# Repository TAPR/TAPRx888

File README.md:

CI docs for design

Source: design @ 3424534723b9f9df8152389dafcadae15212970f
Run: https://github.com/TAPR/TAPRx888/actions/runs/41220624196

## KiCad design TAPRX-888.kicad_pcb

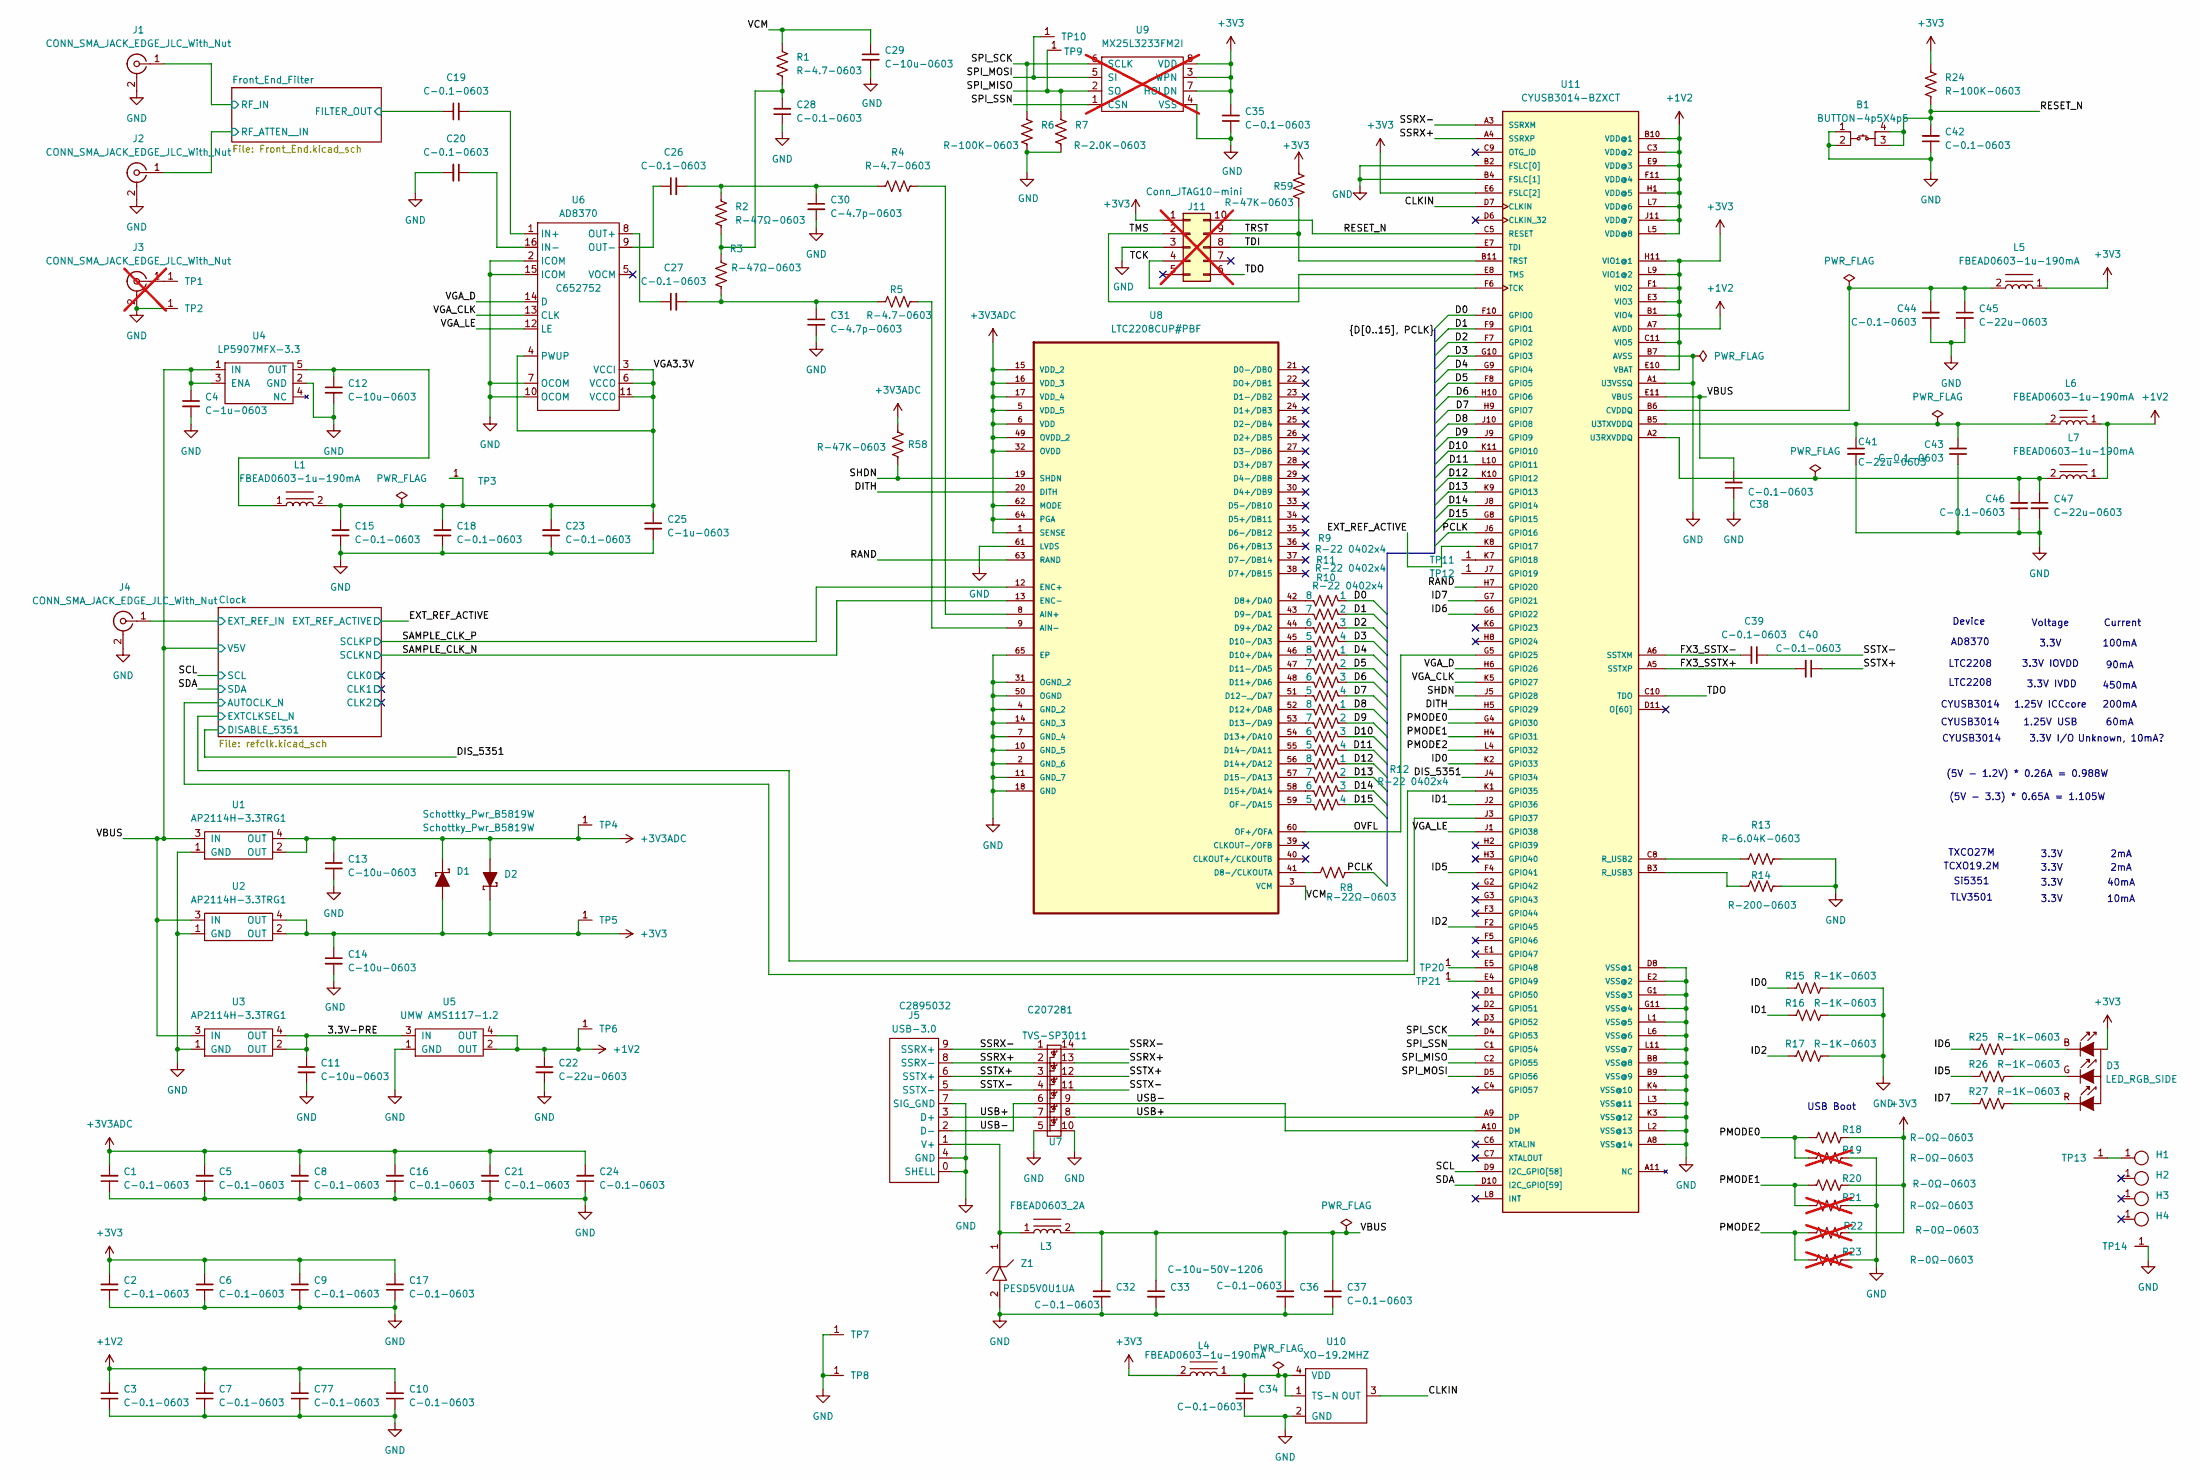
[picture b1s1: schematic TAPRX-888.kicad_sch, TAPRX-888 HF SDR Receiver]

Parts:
B1: BUTTON-4p5X4p5; LCSC Part # C410371
C1, C2, C3, C5, C6, C7, C8, C9, C10, C15, C16, C17, C18, C19, C20, C21, C23, C24, C26, C27, C28, C32, C34, C35, C36, C37, C38, C39, C40, C42, C43, C44, C46, C77: C-0.1-0603; C_0603; LCSC Part # C14663
C4, C25: C-1u-0603; C_0603; LCSC Part # C15849
C11, C12, C13, C14, C29: C-10u-0603; C_0603; LCSC Part # C96446
C22, C41, C45, C47: C-22u-0603; C_0603; LCSC Part # C59461
C30, C31: C-4.7p-0603; C_0603; LCSC Part # C1669
C33: C-10u-50V-1206; PAD_1206; LCSC Part # C13585
D1, D2: Schottky_Pwr_B5819W; SOD-123; LCSC Part # C8598
D3: LED_RGB_SIDE; LCSC Part # C389528
H1, H2, H3, H4: MountingHole_M2.5-PTH
J1, J2, J4: CONN_SMA_JACK_EDGE_JLC_With_Nut; SMA_Jack_EdgeMount_JLC_With_Nut; LCSC Part # C914558
J3: CONN_SMA_JACK_EDGE_JLC_With_Nut; SMA_Jack_EdgeMount_JLC_With_Nut; LCSC Part # C914558; not fitted
J5: USB-3.0; LCSC Part # C2895032
J11: Conn_JTAG10-mini; CONN-JTAG10-mini; LCSC Part # C17362550; not fitted
L1, L4, L5, L6, L7: FBEAD0603-1u-190mA; 0603; LCSC Part # C307748
L2: TIS_LOGO; TIS-Logo
L3: FBEAD0603_2A; 0603; LCSC Part # C14709
R1, R4, R5: R-4.7-0603; PAD_0603; LCSC Part # C23164
R2, R3: R-47Ω-0603; PAD_0603; LCSC Part # C23179
R6, R24: R-100K-0603; PAD_0603; LCSC Part # C25803
R7: R-2.0K-0603; PAD_0603; LCSC Part # C22975
R8: R-22Ω-0603; PAD_0603; LCSC Part # C23345
R9, R10, R11, R12: R-22 0402x4; 4D02; LCSC Part # C25499
R13: R-6.04K-0603; PAD_0603; LCSC Part # C25977
R14: R-200-0603; PAD_0603; LCSC Part # C8218
R15, R16, R17, R25, R26, R27: R-1K-0603; PAD_0603; LCSC Part # C21190
R18, R20: R-0Ω-0603; PAD_0603; LCSC Part # C21189
R19, R21, R22, R23: R-0Ω-0603; PAD_0603; LCSC Part # C21189; not fitted
R58, R59: R-47K-0603; PAD_0603; LCSC Part # C25819
TP1, TP2, TP3, TP4, TP5, TP6, TP7, TP8, TP9, TP10, TP13, TP14: TP
TP11, TP12: TP; TP-Tiny
TP20, TP21: TP-TINY; TP-Tiny
U1, U2, U3: AP2114H-3.3TRG1; SOT-223_THERMAL; LCSC Part # C150716
U4: LP5907MFX-3.3; SOT-23-5; LCSC Part # C80670
U5: UMW AMS1117-1.2; SOT-223_THERMAL; LCSC Part # C347218
U6: AD8370; TSSOP-16-Thermal; LCSC Part # C652752
U7: TVS-SP3011; SP3011; LCSC Part # C207281
U8: LTC2208CUP#PBF; QFN-64_EP_9.5x9.5_Pitch0.5mm; MPN LTC2208CUP#PBF; LCSC Part # C7458386
U9: MX25L3233FM2I; SOIC-8-dual; LCSC Part # C190802; not fitted
U10: XO-19.2MHZ; SMD-2520; LCSC Part # C49304731
U11: CYUSB3014-BZXCT; BGA-121; DigiKey_Part_Number 448-CYUSB3014-BZXCTTR-ND
Z1: PESD5V0U1UA; SOD-323; LCSC Part # C5380401

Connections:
+1V2: C3.2, C7.2, C10.2, C22.1, C77.2, L6.1, L7.1, TP6.1, U5.2 (OUT), U5.4 (OUT), U11.A7 (AVDD), U11.B10 (VDD@1), U11.C3 (VDD@2), U11.E9 (VDD@3), U11.F11 (VDD@4), U11.H1 (VDD@5), U11.J11 (VDD@7), U11.L5 (VDD@8), U11.L7 (VDD@6)
+3V3: C2.2, C6.2, C9.2, C14.1, C17.2, C35.2, D1.2 (A), D2.1 (K), D3.1 (C), J11.1, L4.2, L5.1, R18.2, R20.2, R22.2, R24.1, R59.1, TP5.1, U2.2 (OUT), U2.4 (OUT), U9.3 (WPN), U9.7 (HOLDN), U9.8 (VDD), U11.B1 (VIO4), U11.C11 (VIO5), U11.E3 (VIO3), U11.E6 (FSLC[2]), U11.E10 (VBAT), U11.F1 (VIO2), U11.H11 (VIO1@1), U11.L9 (VIO1@2); also elsewhere on the board
+3V3ADC: C1.2, C5.2, C8.2, C13.1, C16.2, C21.2, C24.2, D1.1 (K), D2.2 (A), R58.1, TP4.1, U1.2 (OUT), U1.4 (OUT), U8.1 (SENSE), U8.5 (VDD_5), U8.6 (VDD), U8.15 (VDD_2), U8.16 (VDD_3), U8.17 (VDD_4), U8.32 (OVDD), U8.49 (OVDD_2), U8.62 (MODE), U8.64 (PGA)
/3.3V-PRE: C11.1, U3.2 (OUT), U3.4 (OUT), U5.3 (IN)
/CLKIN: U10.3 (OUT), U11.D7 (CLKIN)
/Clock/AUTOCLK_N: U11.J3 (GPIO37); also elsewhere on the board
/Clock/EXTCLKSEL_N: U11.K1 (GPIO35); also elsewhere on the board
/Clock/EXT_REF_IN: J4.1 (In); also elsewhere on the board
/D0: R9.1, U11.F10 (GPIO0)
/D1: R9.2, U11.F9 (GPIO1)
/D2: R9.3, U11.F7 (GPIO2)
/D3: R9.4, U11.G10 (GPIO3)
/D4: R10.1, U11.G9 (GPIO4)
/D5: R10.2, U11.F8 (GPIO5)
/D6: R10.3, U11.H10 (GPIO6)
/D7: R10.4, U11.H9 (GPIO7)
/D8: R11.1, U11.J10 (GPIO8)
/D9: R11.2, U11.J9 (GPIO9)
/D10: R11.3, U11.K11 (GPIO10)
/D11: R11.4, U11.L10 (GPIO11)
/D12: R12.1, U11.K10 (GPIO12)
/D13: R12.2, U11.K9 (GPIO13)
/D14: R12.3, U11.J8 (GPIO14)
/D15: R12.4, U11.G8 (GPIO15)
/DIS_5351: U11.J4 (GPIO34); also elsewhere on the board
/DITH: U8.20 (DITH), U11.H5 (GPIO29)
/EXT_REF_ACTIVE: U11.K8 (GPIO17); also elsewhere on the board
/FX3_SSTX+: C40.2, U11.A5 (SSTXP)
/FX3_SSTX-: C39.2, U11.A6 (SSTXM)
/Front_End_Filter/FILTER_OUT: C19.1; also elsewhere on the board
/Front_End_Filter/RF_ATTEN__IN: J2.1 (In); also elsewhere on the board
/Front_End_Filter/RF_IN: J1.1 (In); also elsewhere on the board
/ID0: R15.1, U11.K2 (GPIO33)
/ID1: R16.1, U11.J2 (GPIO36)
/ID2: R17.1, U11.F2 (GPIO45)
/ID5: R26.1, U11.F4 (GPIO41)
/ID6: R25.1, U11.G6 (GPIO22)
/ID7: R27.1, U11.G7 (GPIO21)
/OVFL: U8.60 (OF+/OFA), U11.G5 (GPIO25)
/PCLK: R8.2, U11.J6 (GPIO16)
/PMODE0: R18.1, R19.1, U11.G4 (GPIO30)
/PMODE1: R20.1, R21.1, U11.H4 (GPIO31)
/PMODE2: R22.1, R23.1, U11.L4 (GPIO32)
/RAND: U8.63 (RAND), U11.H7 (GPIO20)
/RESET_N: B1.3, B1.4, C42.2, J11.10, R24.2, U11.C5 (RESET)
/SAMPLE_CLK_N: U8.13 (ENC-); also elsewhere on the board
/SAMPLE_CLK_P: U8.12 (ENC+); also elsewhere on the board
/SCL: U11.D9 (I2C_GPIO[58]); also elsewhere on the board
/SDA: U11.D10 (I2C_GPIO[59]); also elsewhere on the board
/SHDN: R58.2, U8.19 (SHDN), U11.J5 (GPIO28)
/SPI_MISO: R7.1, TP9.1, U9.2 (SO), U11.C2 (GPIO55)
/SPI_MOSI: TP10.1, U9.5 (SI), U11.D5 (GPIO56)
/SPI_SCK: R6.1, U9.6 (SCLK), U11.D4 (GPIO53)
/SPI_SSN: U9.1 (CSN), U11.C1 (GPIO54)
/SSRX+: J5.8 (SSRX-), U7.2, U7.13, U11.A4 (SSRXP)
/SSRX-: J5.9 (SSRX+), U7.1, U7.14, U11.A3 (SSRXM)
/SSTX+: C40.1, J5.6 (SSTX+), U7.3, U7.12
/SSTX-: C39.1, J5.5 (SSTX-), U7.4, U7.11
/TCK: J11.4, U11.F6 (TCK)
/TDI: J11.8, U11.E7 (TDI)
/TDO: J11.6, U11.C10 (TDO)
/TMS: J11.2, U11.E8 (TMS)
/TRST: J11.9, R59.2, U11.B11 (TRST)
/USB+: J5.3 (D+), U7.7, U7.8, U11.A9 (DP)
/USB-: J5.2 (D-), U7.6, U7.9, U11.A10 (DM)
/VBUS: C4.1, C32.2, C33.1, C36.2, C37.2, C38.2, L3.2, U1.3 (IN), U2.3 (IN), U3.3 (IN), U4.1 (IN), U4.3 (ENA), U11.E11 (VBUS); also elsewhere on the board
/VCM: C29.1, R1.1, U8.3 (VCM)
/VGA3.3V: C15.2, C18.2, C23.2, C25.1, L1.2, TP3.1, U6.3 (VCCI), U6.4 (PWUP), U6.6 (VCCO), U6.11 (VCCO)
/VGA_CLK: U6.13 (CLK), U11.K5 (GPIO27)
/VGA_D: U6.14 (D), U11.H6 (GPIO26)
/VGA_LE: U6.12 (LE), U11.J1 (GPIO38)
GND: B1.1, B1.2, C1.1, C2.1, C3.1, C4.2, C5.1, C6.1, C7.1, C8.1, C9.1, C10.1, C11.2, C12.2, C13.2, C14.2, C15.1, C16.1, C17.1, C18.1, C20.2, C21.1, C22.2, C23.1, C24.1, C25.2, C28.1, C29.2, C30.2, C31.2, C32.1, C33.2, C34.1, C35.1, C36.1, C37.1, C38.1, C41.2, C42.1, C43.1, C44.1, C45.2, C46.1, C47.2, C77.1, J1.2 (Ext), J2.2 (Ext), J3.2 (Ext), J4.2 (Ext), J5.0 (SHELL), J5.4 (GND), J5.7 (SIG_GND), J11.3, R6.2, R7.2, R13.2, R14.2, R15.2, R16.2, R17.2, R19.2, R21.2, R23.2, TP2.1, TP7.1, TP8.1, TP14.1, U1.1 (GND), U2.1 (GND), U3.1 (GND), U4.2 (GND), U5.1 (GND), U6.2 (ICOM), U6.7 (OCOM), U6.10 (OCOM), U6.15 (ICOM), U7.5, U7.10, U8.2 (GND_6), U8.4 (GND_2), U8.7 (GND_4), U8.10 (GND_5), U8.11 (GND_7), U8.14 (GND_3), U8.18 (GND), U8.31 (OGND_2), U8.50 (OGND), U8.61 (LVDS), U8.65 (EP), U9.4 (VSS), U10.2 (GND), U11.A1 (U3VSSQ), U11.A8 (VSS@14), U11.B2 (FSLC[0]), U11.B4 (FSLC[1]), U11.B7 (AVSS), U11.B8 (VSS@8), U11.B9 (VSS@9), U11.D8 (VSS@1), U11.E2 (VSS@2), U11.G1 (VSS@3), U11.G11 (VSS@4), U11.K3 (VSS@12), U11.K4 (VSS@10), U11.L1 (VSS@5), U11.L2 (VSS@13), U11.L3 (VSS@11), U11.L6 (VSS@6), U11.L11 (VSS@7), Z1.2; also elsewhere on the board
unnamed: C26.2, C30.1, R2.1, R4.1
unnamed: C27.2, C31.1, R3.2, R5.1
unnamed: C28.2, R1.2, R2.2, R3.1
unnamed: D3.2 (B), R25.2
unnamed: D3.3 (G), R26.2
unnamed: D3.4 (R), R27.2
unnamed: H1.1, TP13.1
unnamed: J3.1 (In), TP1.1
unnamed: J5.1 (V+), L3.1, Z1.1
unnamed: C12.1, L1.1, U4.5 (OUT)
unnamed: C19.2, U6.1 (IN+)
unnamed: C20.1, U6.16 (IN-)
unnamed: C27.1, U6.8 (OUT+)
unnamed: C26.1, U6.9 (OUT-)
unnamed: R4.2, U8.8 (AIN+)
unnamed: R5.2, U8.9 (AIN-)
unnamed: R9.8, U8.42 (D8+/DA0)
unnamed: R8.1, U8.41 (D8-/CLKOUTA)
unnamed: R9.6, U8.44 (D9+/DA2)
unnamed: R9.7, U8.43 (D9-/DA1)
unnamed: R10.8, U8.46 (D10+/DA4)
unnamed: R9.5, U8.45 (D10-/DA3)
unnamed: R10.6, U8.48 (D11+/DA6)
unnamed: R10.7, U8.47 (D11-/DA5)
unnamed: R11.8, U8.52 (D12+/DA8)
unnamed: R10.5, U8.51 (D12-_/DA7)
unnamed: R11.6, U8.54 (D13+/DA10)
unnamed: R11.7, U8.53 (D13-/DA9)
unnamed: R12.8, U8.56 (D14+/DA12)
unnamed: R11.5, U8.55 (D14-/DA11)
unnamed: R12.6, U8.58 (D15+/DA14)
unnamed: R12.7, U8.57 (D15-/DA13)
unnamed: R12.5, U8.59 (OF-/DA15)
unnamed: C34.2, L4.1, U10.1 (TS-N), U10.4 (VDD)
unnamed: C44.2, C45.1, L5.2, U11.B6 (CVDDQ)
unnamed: TP11.1, U11.K7 (GPIO18)
unnamed: TP12.1, U11.J7 (GPIO19)
unnamed: TP20.1, U11.E5 (GPIO48)
unnamed: TP21.1, U11.E4 (GPIO49)
unnamed: R13.1, U11.C8 (R_USB2)
unnamed: R14.1, U11.B3 (R_USB3)
unnamed: C46.2, C47.1, L7.2, U11.A2 (U3RXVDDQ)
unnamed: C41.1, C43.2, L6.2, U11.B5 (U3TXVDDQ)

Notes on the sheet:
3.3V
CYUSB3014
TCXO19.2M
3.3V IOVDD
2mA
TXCO27M
1.25V USB
LTC2208
450mA
3.3V IVDD
200mA
10mA
100mA
Voltage
TLV3501
(5V - 3.3) * 0.65A = 1.105W
Si5351
USB Boot
90mA
1.25V ICCcore
Unknown, 10mA?
AD8370
40mA
60mA
Device
Current
3.3V I/O
(5V - 1.2V) * 0.26A = 0.988W

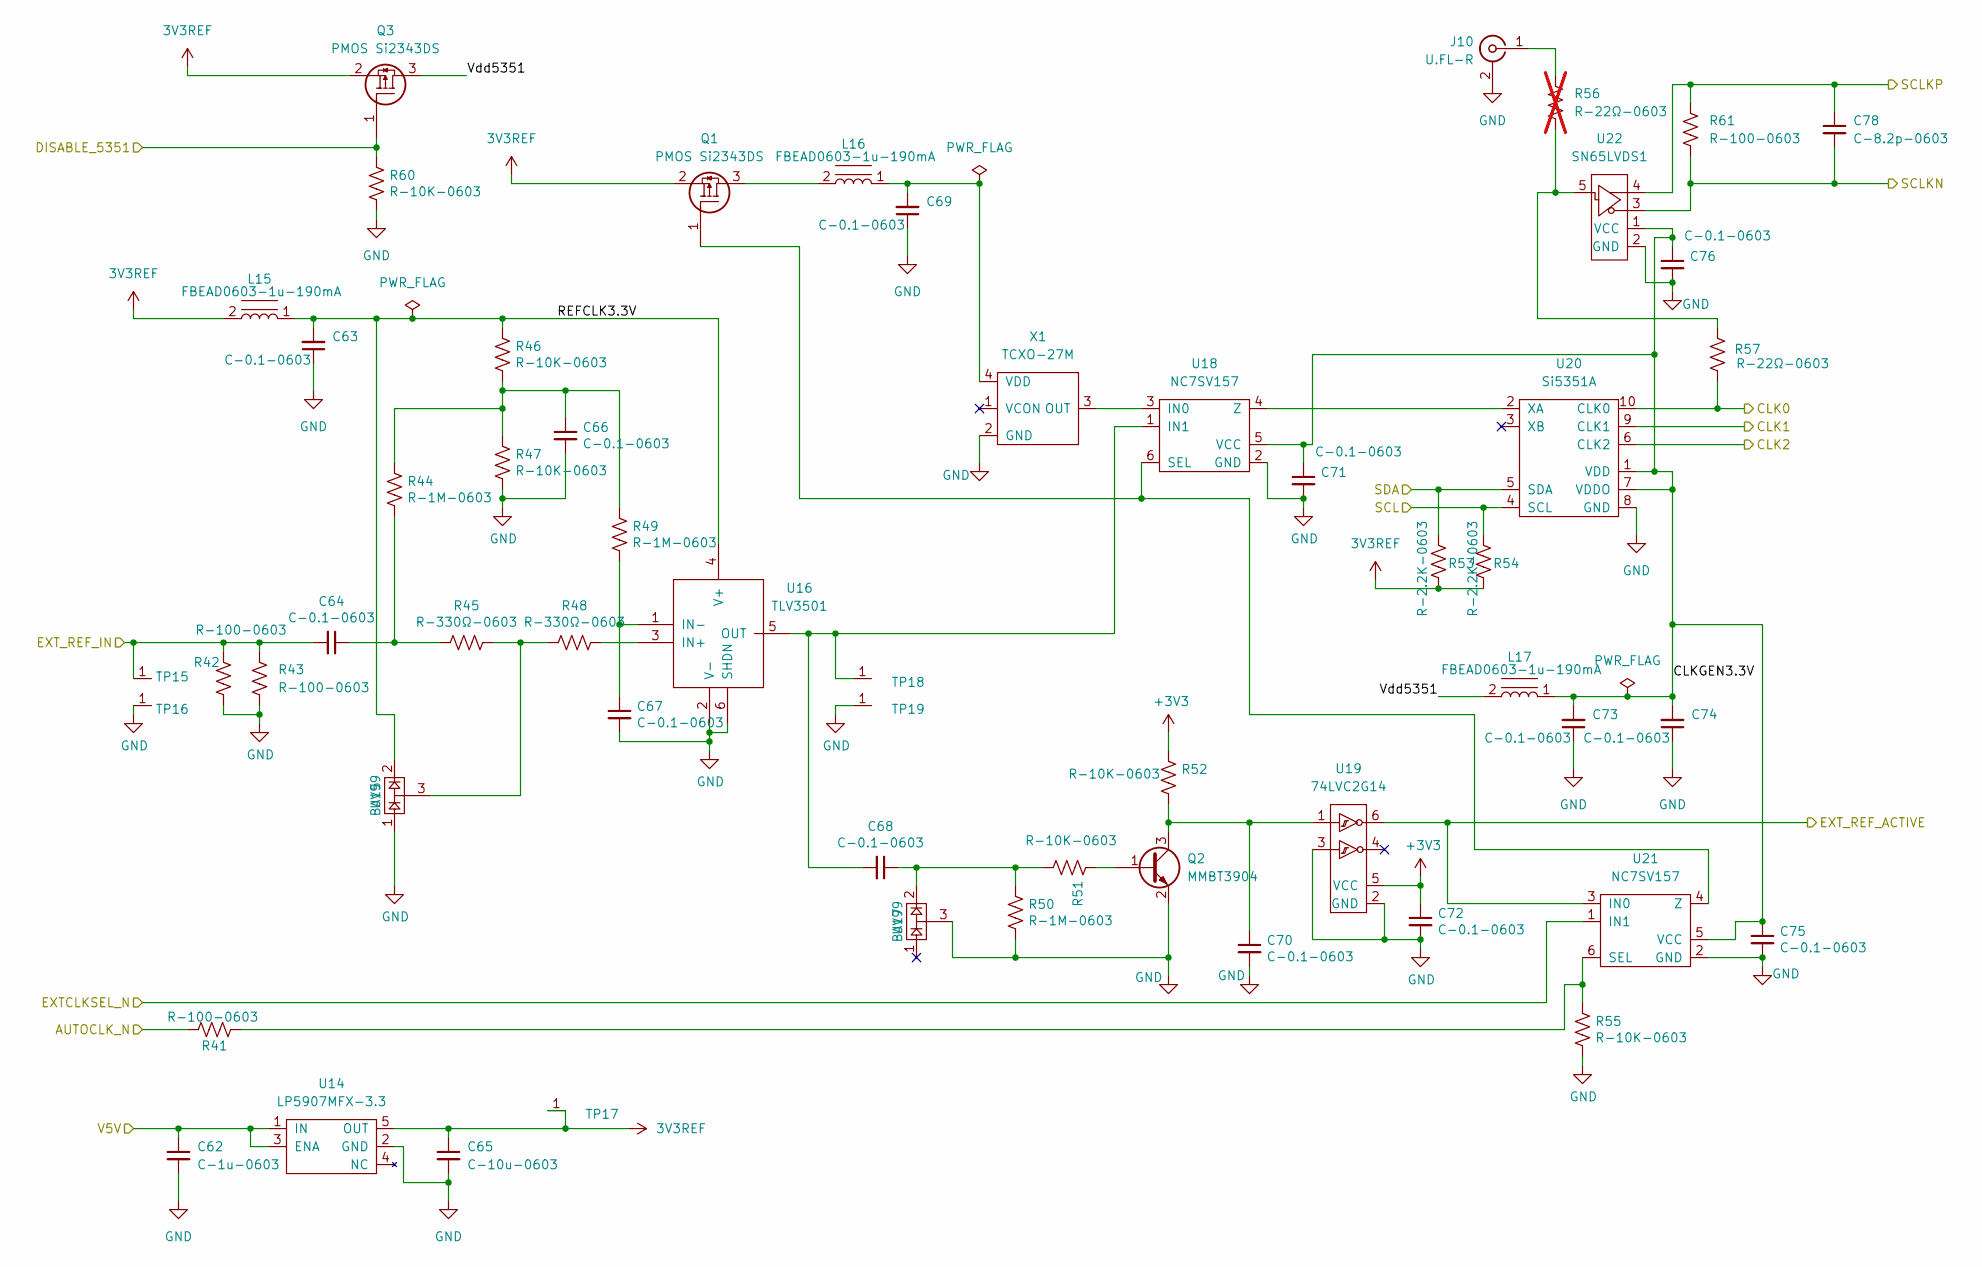
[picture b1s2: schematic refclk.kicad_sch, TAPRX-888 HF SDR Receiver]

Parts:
C62: C-1u-0603; C_0603; LCSC Part # C15849
C63, C64, C66, C67, C68, C69, C70, C71, C72, C73, C74, C75, C76: C-0.1-0603; C_0603; LCSC Part # C14663
C65: C-10u-0603; C_0603; LCSC Part # C96446
C78: C-8.2p-0603; C_0603; LCSC Part # C962145
J10: U.FL-R; HRS_U.FL-R-SMT(01); LCSC Part # C88374
L15, L16, L17: FBEAD0603-1u-190mA; 0603; LCSC Part # C307748
Q1, Q3: PMOS Si2343DS; SOT-23; LCSC Part # C6903
Q2: MMBT3904; SOT-23; LCSC Part # C20526
R41, R42, R43, R61: R-100-0603; PAD_0603; LCSC Part # C22775
R44, R49, R50: R-1M-0603; PAD_0603; LCSC Part # C22935
R45, R48: R-330Ω-0603; PAD_0603; LCSC Part # C23138
R46, R47, R51, R52, R55, R60: R-10K-0603; PAD_0603; LCSC Part # C25804
R53, R54: R-2.2K-0603; PAD_0603; LCSC Part # C4190
R56: R-22Ω-0603; PAD_0603; LCSC Part # C23345; not fitted
R57: R-22Ω-0603; PAD_0603; LCSC Part # C23345
TP15, TP16, TP17, TP18, TP19: TP
U14: LP5907MFX-3.3; SOT-23-5; LCSC Part # C80670
U15, U17: BAV99; SOT-23; LCSC Part # C78088
U16: TLV3501; SOT-23-6; LCSC Part # C193413
U18, U21: NC7SV157; SC-70-6; LCSC Part # C184123
U19: 74LVC2G14; SC-70-6_rot90; LCSC Part # C19829575
U20: Si5351A; MSOP-10_W3mm; LCSC Part # C504891
U22: SN65LVDS1; SOT-23-5; LCSC Part # C465731
X1: TCXO-27M; TCXO-3225; LCSC Part # C5203549

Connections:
3V3REF: C65.1, L15.2, Q1.2 (S), Q3.2 (S), R53.2, R54.2, TP17.1, U14.5 (OUT)
+3V3: C72.1, R52.1, U19.5 (VCC); also elsewhere on the board
/Clock/AUTOCLK_N: R41.1; also elsewhere on the board
/Clock/CLK0: R57.2, U20.10 (CLK0)
/Clock/CLK1: U20.9 (CLK1)
/Clock/CLK2: U20.6 (CLK2)
/Clock/CLKGEN3.3V: C71.1, C73.2, C74.2, C75.1, C76.1, L17.1, U18.5 (VCC), U20.1 (VDD), U20.7 (VDDO), U21.5 (VCC), U22.1 (VCC)
/Clock/EXTCLKSEL_N: U21.1 (IN1); also elsewhere on the board
/Clock/EXT_REF_IN: C64.2, R42.1, R43.1, TP15.1; also elsewhere on the board
/Clock/REFCLK3.3V: C63.2, L15.1, R46.1, U15.2, U16.4 (V+)
/Clock/Vdd5351: L17.2, Q3.3 (D)
/DIS_5351: Q3.1 (G), R60.1; also elsewhere on the board
/EXT_REF_ACTIVE: U19.6, U21.3 (IN0); also elsewhere on the board
/SAMPLE_CLK_N: C78.2, R61.2, U22.3; also elsewhere on the board
/SAMPLE_CLK_P: C78.1, R61.1, U22.4; also elsewhere on the board
/SCL: R54.1, U20.4 (SCL); also elsewhere on the board
/SDA: R53.1, U20.5 (SDA); also elsewhere on the board
/VBUS: C62.1, U14.1 (IN), U14.3 (ENA); also elsewhere on the board
GND: C62.2, C63.1, C65.2, C66.2, C67.2, C69.1, C70.2, C71.2, C72.2, C73.1, C74.1, C75.2, C76.2, J10.2 (Ext), Q2.2 (E), R42.2, R43.2, R47.2, R50.2, R55.2, R60.2, TP16.1, TP19.1, U14.2 (GND), U15.1, U16.2 (V-), U16.6 (SHDN), U17.3, U18.2 (GND), U19.2 (GND), U19.3, U20.8 (GND), U21.2 (GND), U22.2 (GND), X1.2 (GND); also elsewhere on the board
unnamed: C64.1, R44.2, R45.2
unnamed: C66.1, R44.1, R46.2, R47.1, R49.1
unnamed: C68.1, R50.1, R51.2, U17.2
unnamed: J10.1 (In), R56.1
unnamed: L16.2, Q1.3 (D)
unnamed: Q1.1 (G), U18.6 (SEL), U21.4 (Z)
unnamed: Q2.1 (B), R51.1
unnamed: C70.1, Q2.3 (C), R52.2, U19.1
unnamed: R45.1, R48.2, U15.3
unnamed: R56.2, R57.1, U22.5
unnamed: R48.1, U16.3 (IN+)
unnamed: C67.1, R49.2, U16.1 (IN-)
unnamed: C68.2, TP18.1, U16.5 (OUT), U18.1 (IN1)
unnamed: U18.3 (IN0), X1.3 (OUT)
unnamed: U18.4 (Z), U20.2 (XA)
unnamed: R41.2, R55.1, U21.6 (SEL)
unnamed: C69.2, L16.1, X1.4 (VDD)

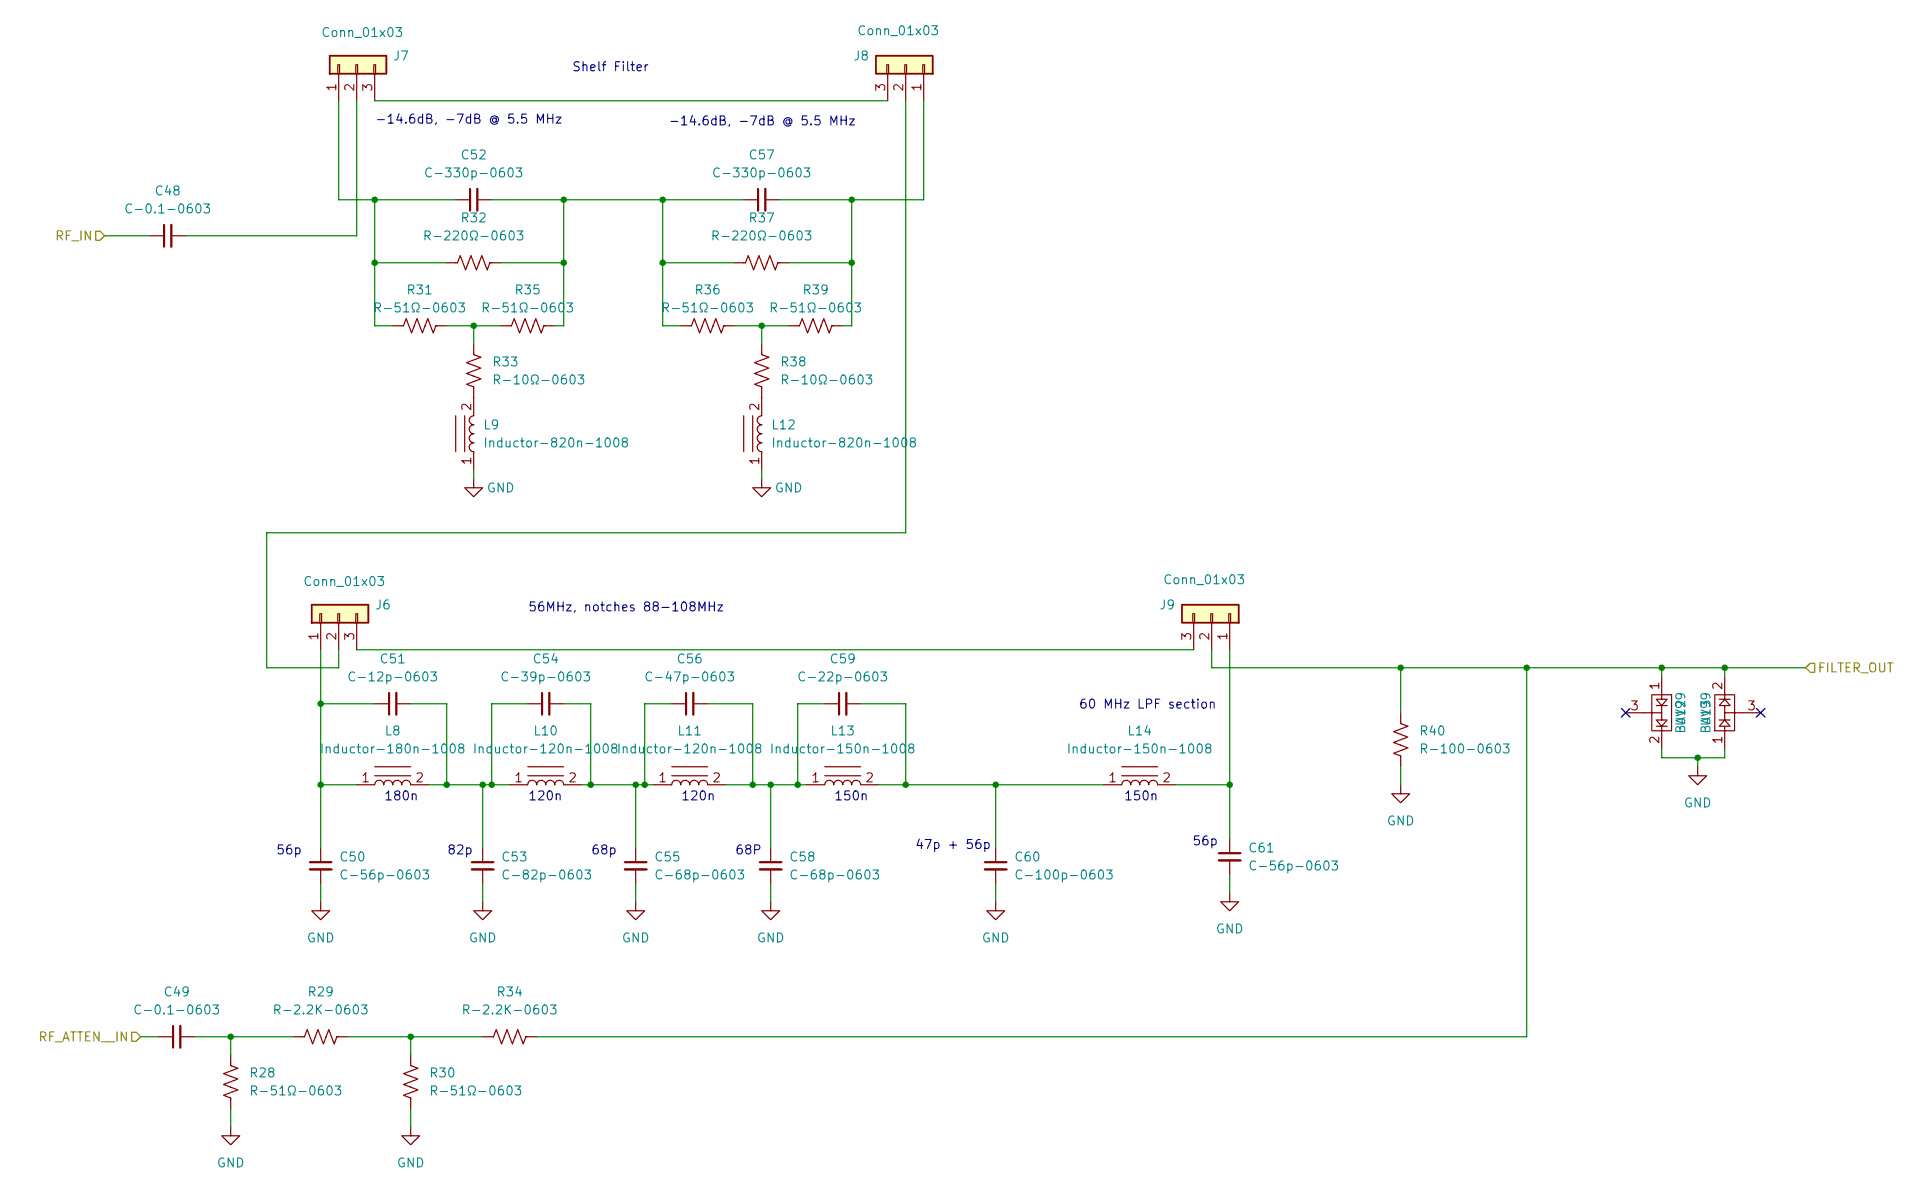
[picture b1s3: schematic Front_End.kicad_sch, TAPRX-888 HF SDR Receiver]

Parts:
C48, C49: C-0.1-0603; C_0603; LCSC Part # C14663
C50, C61: C-56p-0603; C_0603; LCSC Part # C107053
C51: C-12p-0603; C_0603; LCSC Part # C576801
C52, C57: C-330p-0603; C_0603; LCSC Part # C327088
C53: C-82p-0603; C_0603; LCSC Part # C1683
C54: C-39p-0603; C_0603; LCSC Part # C107049
C55, C58: C-68p-0603; C_0603; LCSC Part # C62782
C56: C-47p-0603; C_0603; LCSC Part # C105622
C59: C-22p-0603; C_0603; LCSC Part # C105620
C60: C-100p-0603; C_0603; LCSC Part # C14665
J6, J7, J8, J9: Conn_01x03; Pin_Header_Straight_1x03_Pitch2.54mm; LCSC Part # C2937625
L8: Inductor-180n-1008; Murata2U; LCSC Part # C162664
L9, L12: Inductor-820n-1008; Murata2U; LCSC Part # C701161
L10, L11: Inductor-120n-1008; Murata2U; LCSC Part # C703706
L13, L14: Inductor-150n-1008; Murata2U; LCSC Part # C2043109
R28, R30, R31, R35, R36, R39: R-51Ω-0603; PAD_0603; LCSC Part # C23197
R29, R34: R-2.2K-0603; PAD_0603; LCSC Part # C4190
R32, R37: R-220Ω-0603; PAD_0603; LCSC Part # C22962
R33, R38: R-10Ω-0603; PAD_0603; LCSC Part # C22859
R40: R-100-0603; PAD_0603; LCSC Part # C22775
U12, U13: BAV99; SOT-23; LCSC Part # C78088

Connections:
/Front_End_Filter/FILTER_OUT: J9.2, R34.2, R40.1, U12.1, U13.2; also elsewhere on the board
/Front_End_Filter/RF_ATTEN__IN: C49.1; also elsewhere on the board
/Front_End_Filter/RF_IN: C48.1; also elsewhere on the board
GND: C50.2, C53.2, C55.2, C58.2, C60.2, C61.2, L9.1, L12.1, R28.2, R30.2, R40.2, U12.2, U13.1; also elsewhere on the board
unnamed: C49.2, R28.1, R29.1
unnamed: C51.2, C53.1, C54.1, L8.2, L10.1
unnamed: C52.2, C57.1, R32.2, R35.2, R36.1, R37.1
unnamed: C54.2, C55.1, C56.1, L10.2, L11.1
unnamed: C56.2, C58.1, C59.1, L11.2, L13.1
unnamed: C59.2, C60.1, L13.2, L14.1
unnamed: C50.1, C51.1, J6.1, L8.1
unnamed: J6.2, J8.2
unnamed: J6.3, J9.3
unnamed: C52.1, J7.1, R31.1, R32.1
unnamed: C48.2, J7.2
unnamed: J7.3, J8.3
unnamed: C57.2, J8.1, R37.2, R39.2
unnamed: C61.1, J9.1, L14.2
unnamed: L9.2, R33.2
unnamed: L12.2, R38.2
unnamed: R29.2, R30.1, R34.1
unnamed: R31.2, R33.1, R35.1
unnamed: R36.2, R38.1, R39.1

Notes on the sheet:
82p
47p + 56p
150n
120n
180n
Shelf Filter
56p
68P
68p
-14.6dB, -7dB @ 5.5 MHz
56MHz, notches 88-108MHz
60 MHz LPF section

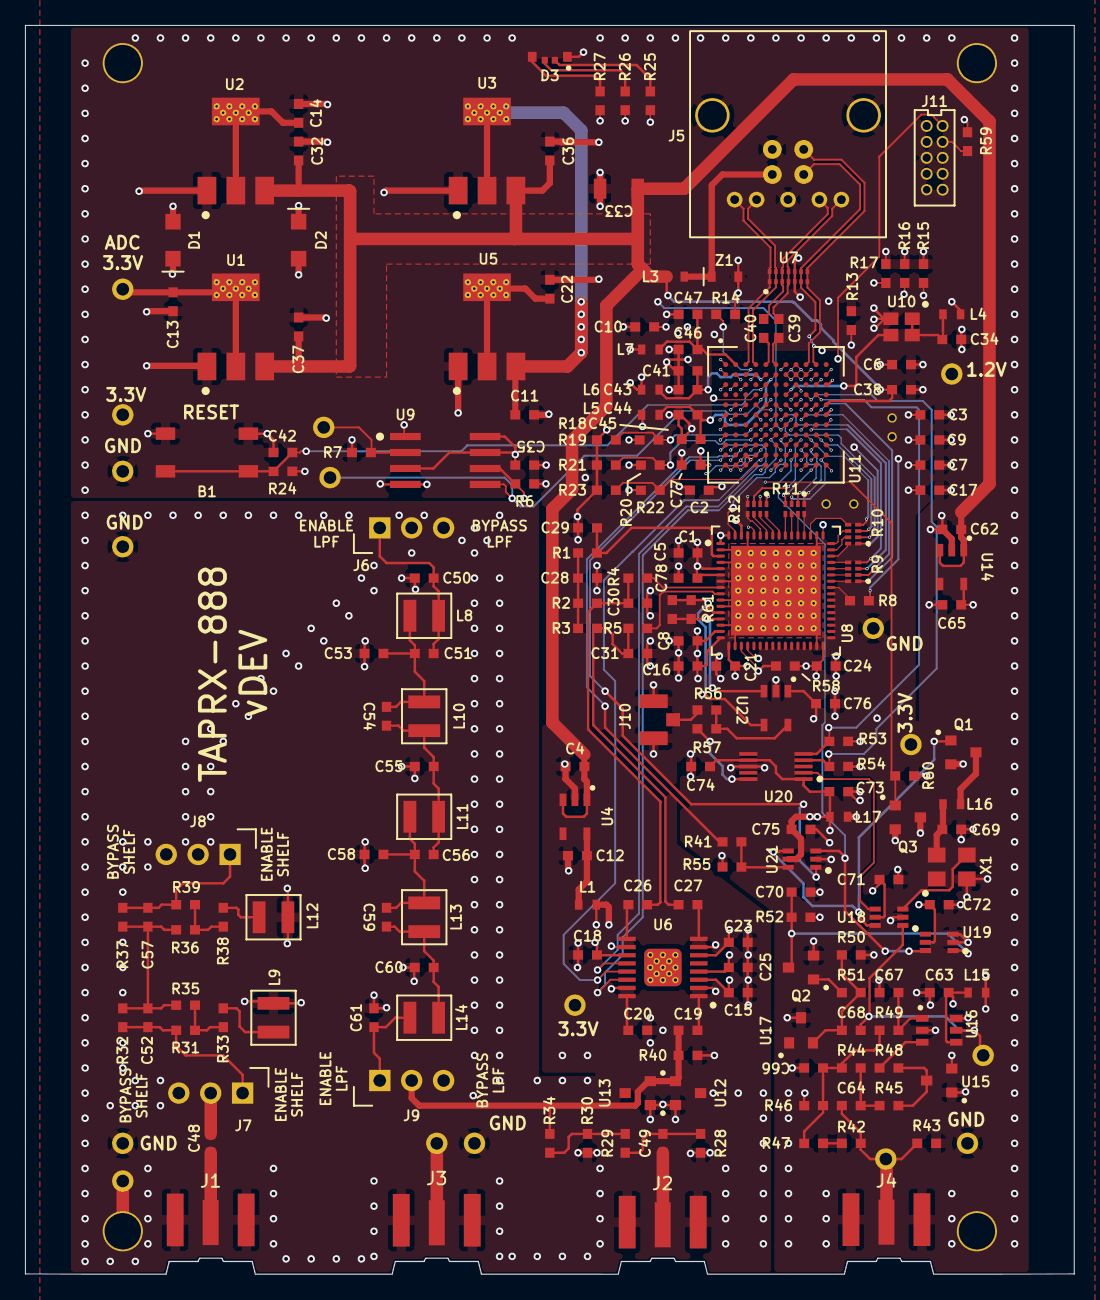
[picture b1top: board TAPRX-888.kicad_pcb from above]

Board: 6 copper layers, 83.5 x 99.4 mm, 223 parts (1 on the bottom side), 156 nets.

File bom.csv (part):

"Reference","Value","Footprint","LCSC"
"B1","BUTTON-4p5X4p5","Library:BUTTON-4p5X4p5","C410371"
"C1","C-0.1-0603","Library:C_0603","C14663"
"C2","C-0.1-0603","Library:C_0603","C14663"
"C3","C-0.1-0603","Library:C_0603","C14663"
"C4","C-1u-0603","Library:C_0603","C15849"
"C5","C-0.1-0603","Library:C_0603","C14663"
"C6","C-0.1-0603","Library:C_0603","C14663"
"C7","C-0.1-0603","Library:C_0603","C14663"
"C8","C-0.1-0603","Library:C_0603","C14663"
"C9","C-0.1-0603","Library:C_0603","C14663"
"C10","C-0.1-0603","Library:C_0603","C14663"
"C11","C-10u-0603","Library:C_0603","C96446"
"C12","C-10u-0603","Library:C_0603","C96446"
"C13","C-10u-0603","Library:C_0603","C96446"
"C14","C-10u-0603","Library:C_0603","C96446"
"C15","C-0.1-0603","Library:C_0603","C14663"
"C16","C-0.1-0603","Library:C_0603","C14663"
"C17","C-0.1-0603","Library:C_0603","C14663"
"C18","C-0.1-0603","Library:C_0603","C14663"
"C19","C-0.1-0603","Library:C_0603","C14663"
"C20","C-0.1-0603","Library:C_0603","C14663"
"C21","C-0.1-0603","Library:C_0603","C14663"
"C22","C-22u-0603","Library:C_0603","C59461"
"C23","C-0.1-0603","Library:C_0603","C14663"
"C24","C-0.1-0603","Library:C_0603","C14663"
"C25","C-1u-0603","Library:C_0603","C15849"
"C26","C-0.1-0603","Library:C_0603","C14663"
"C27","C-0.1-0603","Library:C_0603","C14663"
"C28","C-0.1-0603","Library:C_0603","C14663"
"C29","C-10u-0603","Library:C_0603","C96446"
"C30","C-4.7p-0603","Library:C_0603","C1669"
"C31","C-4.7p-0603","Library:C_0603","C1669"
"C32","C-0.1-0603","Library:C_0603","C14663"
"C33","C-10u-50V-1206","Library:PAD_1206","C13585"
"C34","C-0.1-0603","Library:C_0603","C14663"
"C35","C-0.1-0603","Library:C_0603","C14663"
"C36","C-0.1-0603","Library:C_0603","C14663"
"C37","C-0.1-0603","Library:C_0603","C14663"
"C38","C-0.1-0603","Library:C_0603","C14663"
"C39","C-0.1-0603","Library:C_0603","C14663"
"C40","C-0.1-0603","Library:C_0603","C14663"
"C41","C-22u-0603","Library:C_0603","C59461"
"C42","C-0.1-0603","Library:C_0603","C14663"
"C43","C-0.1-0603","Library:C_0603","C14663"
"C44","C-0.1-0603","Library:C_0603","C14663"
"C45","C-22u-0603","Library:C_0603","C59461"
"C46","C-0.1-0603","Library:C_0603","C14663"
"C47","C-22u-0603","Library:C_0603","C59461"
"C48","C-0.1-0603","Library:C_0603","C14663"
"C49","C-0.1-0603","Library:C_0603","C14663"
"C50","C-56p-0603","Library:C_0603","C107053"
"C51","C-12p-0603","Library:C_0603","C576801"
"C52","C-330p-0603","Library:C_0603","C327088"
"C53","C-82p-0603","Library:C_0603","C1683"
"C54","C-39p-0603","Library:C_0603","C107049"
"C55","C-68p-0603","Library:C_0603","C62782"
"C56","C-47p-0603","Library:C_0603","C105622"
"C57","C-330p-0603","Library:C_0603","C327088"
"C58","C-68p-0603","Library:C_0603","C62782"
"C59","C-22p-0603","Library:C_0603","C105620"
"C60","C-100p-0603","Library:C_0603","C14665"
"C61","C-56p-0603","Library:C_0603","C107053"
"C62","C-1u-0603","Library:C_0603","C15849"
"C63","C-0.1-0603","Library:C_0603","C14663"
"C64","C-0.1-0603","Library:C_0603","C14663"
"C65","C-10u-0603","Library:C_0603","C96446"
"C66","C-0.1-0603","Library:C_0603","C14663"
"C67","C-0.1-0603","Library:C_0603","C14663"
"C68","C-0.1-0603","Library:C_0603","C14663"
"C69","C-0.1-0603","Library:C_0603","C14663"
"C70","C-0.1-0603","Library:C_0603","C14663"
"C71","C-0.1-0603","Library:C_0603","C14663"
"C72","C-0.1-0603","Library:C_0603","C14663"
"C73","C-0.1-0603","Library:C_0603","C14663"
"C74","C-0.1-0603","Library:C_0603","C14663"
"C75","C-0.1-0603","Library:C_0603","C14663"
"C76","C-0.1-0603","Library:C_0603","C14663"
"C77","C-0.1-0603","Library:C_0603","C14663"
"C78","C-8.2p-0603","Library:C_0603","C962145"
"D1","Schottky_Pwr_B5819W","Library:SOD-123","C8598"
"D2","Schottky_Pwr_B5819W","Library:SOD-123","C8598"
"D3","LED_RGB_SIDE","Library:LED_RGB_SIDE","C389528"
"J1","CONN_SMA_JACK_EDGE_JLC_With_Nut","Library:SMA_Jack_EdgeMount_JLC_With_Nut","C914558"
"J2","CONN_SMA_JACK_EDGE_JLC_With_Nut","Library:SMA_Jack_EdgeMount_JLC_With_Nut","C914558"
"J4","CONN_SMA_JACK_EDGE_JLC_With_Nut","Library:SMA_Jack_EdgeMount_JLC_With_Nut","C914558"
"J5","USB-3.0","Library:USB-3.0","C2895032"
"J6","Conn_01x03","Library:Pin_Header_Straight_1x03_Pitch2.54mm","C2937625"
"J7","Conn_01x03","Library:Pin_Header_Straight_1x03_Pitch2.54mm","C2937625"
"J8","Conn_01x03","Library:Pin_Header_Straight_1x03_Pitch2.54mm","C2937625"
"J9","Conn_01x03","Library:Pin_Header_Straight_1x03_Pitch2.54mm","C2937625"
"J10","U.FL-R","Library:HRS_U.FL-R-SMT(01)","C88374"
"L1","FBEAD0603-1u-190mA","Library:0603","C307748"
"L3","FBEAD0603_2A","Library:0603","C14709"
"L4","FBEAD0603-1u-190mA","Library:0603","C307748"
"L5","FBEAD0603-1u-190mA","Library:0603","C307748"
"L6","FBEAD0603-1u-190mA","Library:0603","C307748"
"L7","FBEAD0603-1u-190mA","Library:0603","C307748"
"L8","Inductor-180n-1008","Library:Murata2U","C162664"
"L9","Inductor-820n-1008","Library:Murata2U","C701161"
"L10","Inductor-120n-1008","Library:Murata2U","C703706"
"L11","Inductor-120n-1008","Library:Murata2U","C703706"
"L12","Inductor-820n-1008","Library:Murata2U","C701161"
"L13","Inductor-150n-1008","Library:Murata2U","C2043109"
"L14","Inductor-150n-1008","Library:Murata2U","C2043109"
"L15","FBEAD0603-1u-190mA","Library:0603","C307748"
"L16","FBEAD0603-1u-190mA","Library:0603","C307748"
"L17","FBEAD0603-1u-190mA","Library:0603","C307748"
"Q1","PMOS Si2343DS","Library:SOT-23","C6903"
"Q2","MMBT3904","Library:SOT-23","C20526"
"Q3","PMOS Si2343DS","Library:SOT-23","C6903"
"R1","R-4.7-0603","Library:PAD_0603","C23164"
"R2","R-47Ω-0603","Library:PAD_0603","C23179"
"R3","R-47Ω-0603","Library:PAD_0603","C23179"
"R4","R-4.7-0603","Library:PAD_0603","C23164"
"R5","R-4.7-0603","Library:PAD_0603","C23164"
"R6","R-100K-0603","Library:PAD_0603","C25803"
"R7","R-2.0K-0603","Library:PAD_0603","C22975"
"R8","R-22Ω-0603","Library:PAD_0603","C23345"
"R9","R-22 0402x4","Library:4D02","C25499"
"R10","R-22 0402x4","Library:4D02","C25499"
"R11","R-22 0402x4","Library:4D02","C25499"
"R12","R-22 0402x4","Library:4D02","C25499"
"R13","R-6.04K-0603","Library:PAD_0603","C25977"
"R14","R-200-0603","Library:PAD_0603","C8218"
"R15","R-1K-0603","Library:PAD_0603","C21190"
"R16","R-1K-0603","Library:PAD_0603","C21190"
"R17","R-1K-0603","Library:PAD_0603","C21190"
"R18","R-0Ω-0603","Library:PAD_0603","C21189"
"R20","R-0Ω-0603","Library:PAD_0603","C21189"
"R24","R-100K-0603","Library:PAD_0603","C25803"
"R25","R-1K-0603","Library:PAD_0603","C21190"
"R26","R-1K-0603","Library:PAD_0603","C21190"
"R27","R-1K-0603","Library:PAD_0603","C21190"
"R28","R-51Ω-0603","Library:PAD_0603","C23197"
"R29","R-2.2K-0603","Library:PAD_0603","C4190"
"R30","R-51Ω-0603","Library:PAD_0603","C23197"
"R31","R-51Ω-0603","Library:PAD_0603","C23197"
"R32","R-220Ω-0603","Library:PAD_0603","C22962"
"R33","R-10Ω-0603","Library:PAD_0603","C22859"
"R34","R-2.2K-0603","Library:PAD_0603","C4190"
"R35","R-51Ω-0603","Library:PAD_0603","C23197"
"R36","R-51Ω-0603","Library:PAD_0603","C23197"
"R37","R-220Ω-0603","Library:PAD_0603","C22962"
"R38","R-10Ω-0603","Library:PAD_0603","C22859"
"R39","R-51Ω-0603","Library:PAD_0603","C23197"
"R40","R-100-0603","Library:PAD_0603","C22775"
"R41","R-100-0603","Library:PAD_0603","C22775"
"R42","R-100-0603","Library:PAD_0603","C22775"
"R43","R-100-0603","Library:PAD_0603","C22775"
"R44","R-1M-0603","Library:PAD_0603","C22935"
"R45","R-330Ω-0603","Library:PAD_0603","C23138"
"R46","R-10K-0603","Library:PAD_0603","C25804"
"R47","R-10K-0603","Library:PAD_0603","C25804"
"R48","R-330Ω-0603","Library:PAD_0603","C23138"
"R49","R-1M-0603","Library:PAD_0603","C22935"
"R50","R-1M-0603","Library:PAD_0603","C22935"
"R51","R-10K-0603","Library:PAD_0603","C25804"
"R52","R-10K-0603","Library:PAD_0603","C25804"
"R53","R-2.2K-0603","Library:PAD_0603","C4190"
"R54","R-2.2K-0603","Library:PAD_0603","C4190"
"R55","R-10K-0603","Library:PAD_0603","C25804"
"R57","R-22Ω-0603","Library:PAD_0603","C23345"
"R58","R-47K-0603","Library:PAD_0603","C25819"
"R59","R-47K-0603","Library:PAD_0603","C25819"
"R60","R-10K-0603","Library:PAD_0603","C25804"
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

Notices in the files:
parts and their libraries:
LICENSE: MIT
